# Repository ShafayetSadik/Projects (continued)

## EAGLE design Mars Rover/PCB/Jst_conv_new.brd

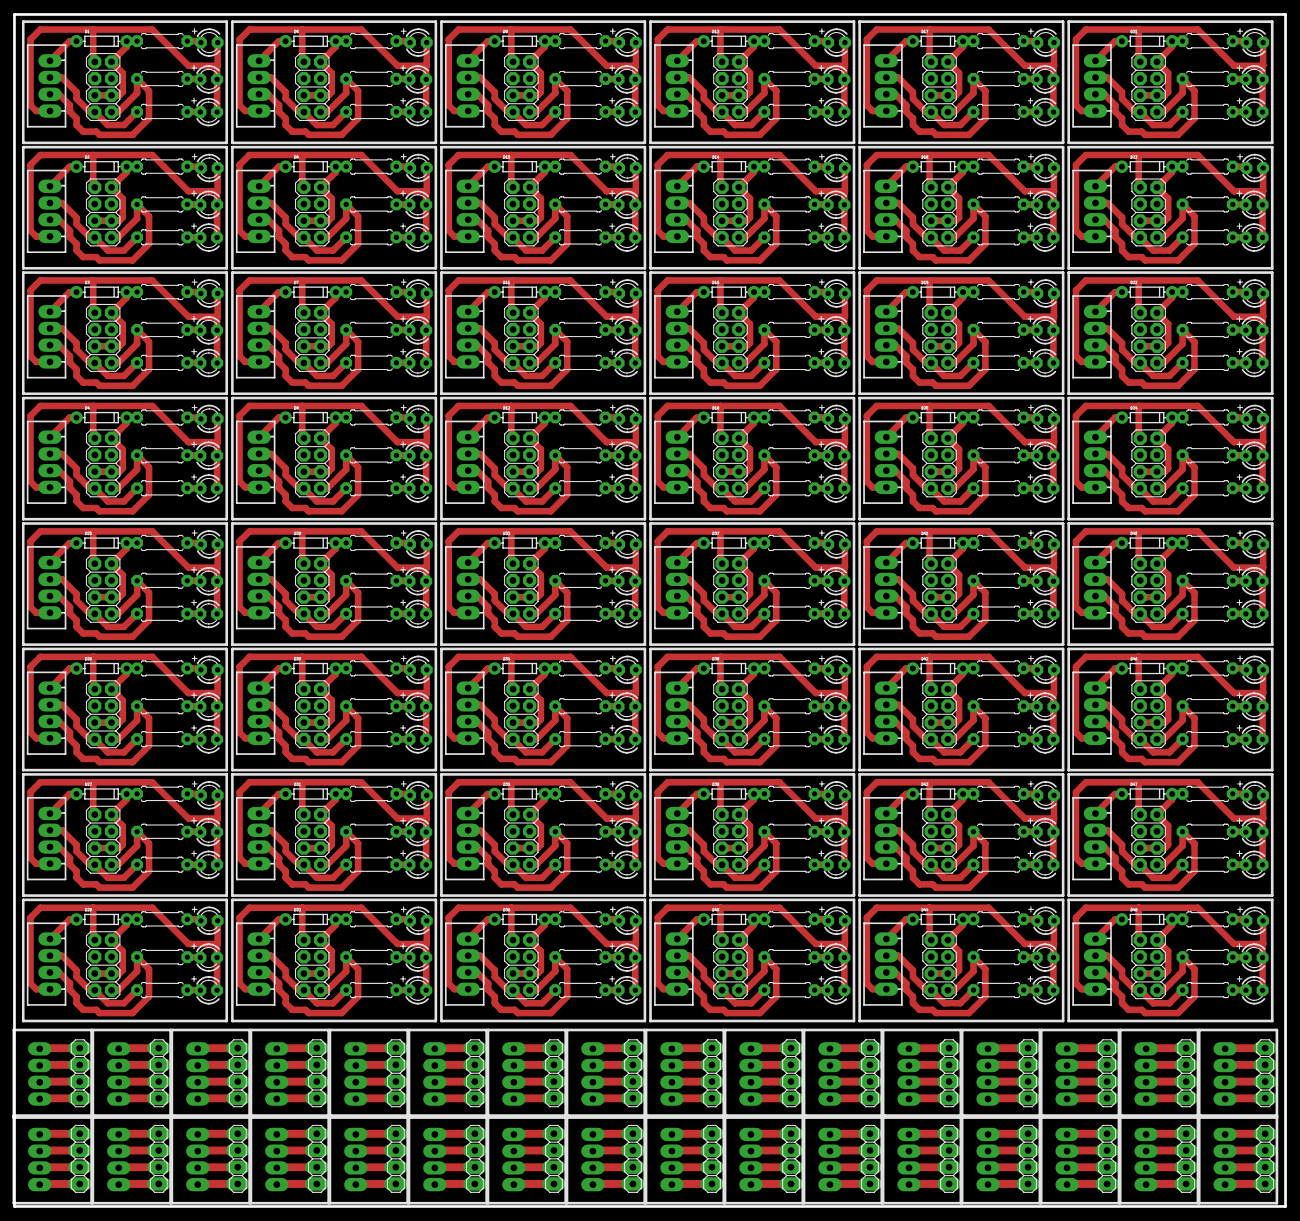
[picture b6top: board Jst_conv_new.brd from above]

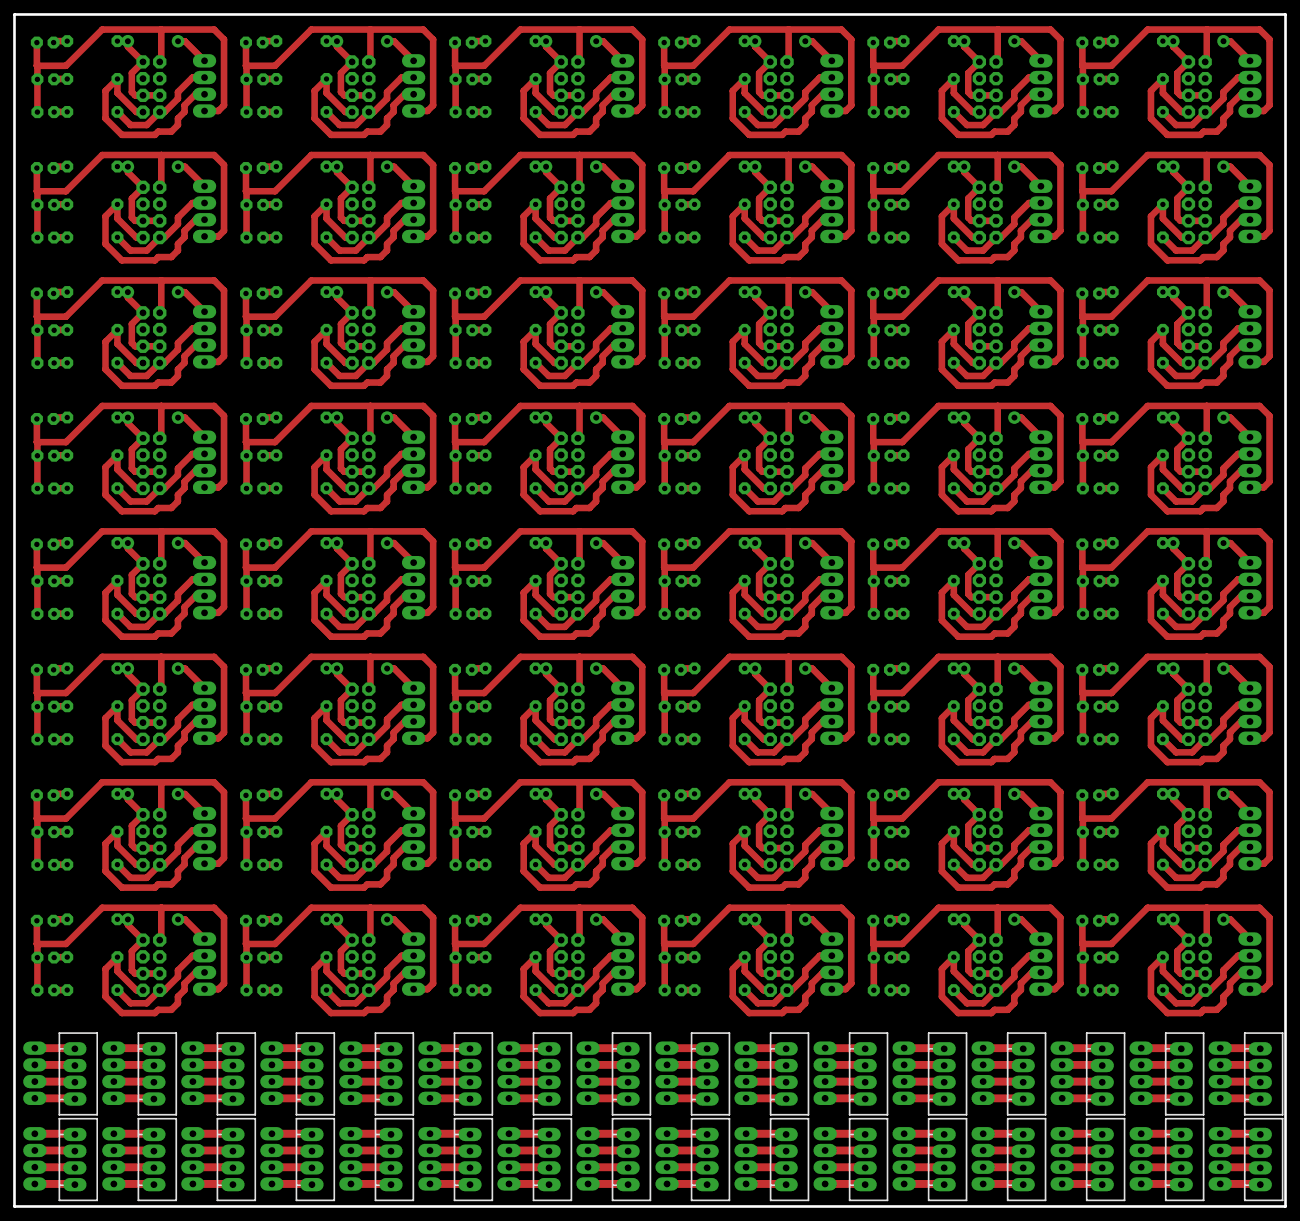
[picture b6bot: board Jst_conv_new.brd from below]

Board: 2 copper layers, 193.0 x 181.0 mm, 496 parts (32 on the bottom side), 512 nets.

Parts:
D1, D2, D3, D4, D5, D6, D7, D8, D9, D10, D11, D12, D13, D14, D15, D16, D17, D18, D19, D20, D21, D22, D23, D24, D25, D26, D27, D28, D29, D30, D31, D32, D33, D34, D35, D36, D37, D38, D39, D40, D41, D42, D43, D44, D45, D46, D47, D48: DO-1N4148
JP1, JP2, JP3, JP4, JP5, JP6, JP7, JP8, JP9, JP10, JP11, JP12, JP13, JP14, JP15, JP16, JP17, JP18, JP19, JP20, JP21, JP22, JP23, JP24, JP25, JP26, JP27, JP28, JP29, JP30, JP31, JP32, JP33, JP34, JP35, JP36, JP37, JP38, JP39, JP40, JP41, JP42, JP43, JP44, JP45, JP46, JP47, JP48: 2X04
JP49, JP50, JP51, JP52, JP53, JP54, JP55, JP56, JP57, JP58, JP59, JP60, JP61, JP62, JP63, JP64, JP65, JP66, JP67, JP68, JP69, JP70, JP71, JP72, JP73, JP74, JP75, JP76, JP77, JP78, JP79, JP80: 1X04
LED1, LED2, LED3, LED4, LED5, LED6, LED7, LED8, LED9, LED10, LED11, LED12, LED13, LED14, LED15, LED16, LED17, LED18, LED19, LED20, LED21, LED22, LED23, LED24, LED25, LED26, LED27, LED28, LED29, LED30, LED31, LED32, LED33, LED34, LED35, LED36, LED37, LED38, LED39, LED40, LED41, LED42, LED43, LED44, LED45, LED46, LED47, LED48, LED49, LED50, LED51, LED52, LED53, LED54, LED55, LED56, LED57, LED58, LED59, LED60, LED61, LED62, LED63, LED64, LED65, LED66, LED67, LED68, LED69, LED70, LED71, LED72, LED73, LED74, LED75, LED76, LED77, LED78, LED79, LED80, LED81, LED82, LED83, LED84, LED85, LED86, LED87, LED88, LED89, LED90, LED91, LED92, LED93, LED94, LED95, LED96, LED97, LED98, LED99, LED100, LED101, LED102, LED103, LED104, LED105, LED106, LED107, LED108, LED109, LED110, LED111, LED112, LED113, LED114, LED115, LED116, LED117, LED118, LED119, LED120, LED121, LED122, LED123, LED124, LED125, LED126, LED127, LED128, LED129, LED130, LED131, LED132, LED133, LED134, LED135, LED136, LED137, LED138, LED139, LED140, LED141, LED142, LED143, LED144: LED3MM
R1, R2, R3, R4, R5, R6, R7, R8, R9, R10, R11, R12, R13, R14, R15, R16, R17, R18, R19, R20, R21, R22, R23, R24, R25, R26, R27, R28, R29, R30, R31, R32, R33, R34, R35, R36, R37, R38, R39, R40, R41, R42, R43, R44, R45, R46, R47, R48, R49, R50, R51, R52, R53, R54, R55, R56, R57, R58, R59, R60, R61, R62, R63, R64, R65, R66, R67, R68, R69, R70, R71, R72, R73, R74, R75, R76, R77, R78, R79, R80, R81, R82, R83, R84, R85, R86, R87, R88, R89, R90, R91, R92, R93, R94, R95, R96, R97, R98, R99, R100, R101, R102, R103, R104, R105, R106, R107, R108, R109, R110, R111, R112, R113, R114, R115, R116, R117, R118, R119, R120, R121, R122, R123, R124, R125, R126, R127, R128, R129, R130, R131, R132, R133, R134, R135, R136, R137, R138, R139, R140, R141, R142, R143, R144: 0207/7
X1, X2, X3, X4, X5, X6, X7, X8, X9, X10, X11, X12, X13, X14, X15, X16, X17, X18, X19, X20, X21, X22, X23, X24, X25, X26, X27, X28, X29, X30, X31, X32, X33, X34, X35, X36, X37, X38, X39, X40, X41, X42, X43, X44, X45, X46, X47, X48, X49, X50, X51, X52, X53, X54, X55, X56, X57, X58, X59, X60, X61, X62, X63, X64, X65, X66, X67, X68, X69, X70, X71, X72, X73, X74, X75, X76, X77, X78, X79, X80: JST-XH-04-PIN-LONG-PAD; JST-XH-04-PACKAGE-LONG-PAD

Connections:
A: JP1.7, R6.2, X1.3
A1: JP2.7, R3.2, X2.3
A2: JP3.7, R9.2, X3.3
A3: JP4.7, R12.2, X4.3
A4: JP5.7, R15.2, X5.3
A5: JP6.7, R18.2, X6.3
A6: JP7.7, R21.2, X7.3
A7: JP8.7, R24.2, X8.3
A8: JP9.7, R27.2, X9.3
A9: JP10.7, R30.2, X10.3
A10: JP11.7, R33.2, X11.3
A11: JP12.7, R36.2, X12.3
A12: JP13.7, R39.2, X13.3
A13: JP14.7, R42.2, X14.3
A14: JP15.7, R45.2, X15.3
A15: JP16.7, R48.2, X16.3
A16: JP17.7, R51.2, X17.3
A17: JP18.7, R54.2, X18.3
A18: JP19.7, R57.2, X19.3
A19: JP20.7, R60.2, X20.3
A20: JP21.7, R63.2, X21.3
A21: JP22.7, R66.2, X22.3
A22: JP23.7, R69.2, X23.3
A23: JP24.7, R72.2, X24.3
A24: JP25.7, R75.2, X25.3
A25: JP26.7, R78.2, X26.3
A26: JP27.7, R81.2, X27.3
A27: JP28.7, R84.2, X28.3
A28: JP29.7, R87.2, X29.3
A29: JP30.7, R90.2, X30.3
A30: JP31.7, R93.2, X31.3
A31: JP32.7, R96.2, X32.3
A32: JP33.7, R99.2, X33.3
A33: JP34.7, R102.2, X34.3
A34: JP35.7, R105.2, X35.3
A35: JP36.7, R108.2, X36.3
A36: JP37.7, R111.2, X37.3
A37: JP38.7, R114.2, X38.3
A38: JP39.7, R117.2, X39.3
A39: JP40.7, R120.2, X40.3
A40: JP41.7, R123.2, X41.3
A41: JP42.7, R126.2, X42.3
A42: JP43.7, R129.2, X43.3
A43: JP44.7, R132.2, X44.3
A44: JP45.7, R135.2, X45.3
A45: JP46.7, R138.2, X46.3
A46: JP47.7, R141.2, X47.3
A47: JP48.7, R144.2, X48.3
B: JP1.8, R4.2, X1.2
B1: JP2.8, R1.2, X2.2
B2: JP3.8, R7.2, X3.2
B3: JP4.8, R10.2, X4.2
B4: JP5.8, R13.2, X5.2
B5: JP6.8, R16.2, X6.2
B6: JP7.8, R19.2, X7.2
B7: JP8.8, R22.2, X8.2
B8: JP9.8, R25.2, X9.2
B9: JP10.8, R28.2, X10.2
B10: JP11.8, R31.2, X11.2
B11: JP12.8, R34.2, X12.2
B12: JP13.8, R37.2, X13.2
B13: JP14.8, R40.2, X14.2
B14: JP15.8, R43.2, X15.2
B15: JP16.8, R46.2, X16.2
B16: JP17.8, R49.2, X17.2
B17: JP18.8, R52.2, X18.2
B18: JP19.8, R55.2, X19.2
B19: JP20.8, R58.2, X20.2
B20: JP21.8, R61.2, X21.2
B21: JP22.8, R64.2, X22.2
B22: JP23.8, R67.2, X23.2
B23: JP24.8, R70.2, X24.2
B24: JP25.8, R73.2, X25.2
B25: JP26.8, R76.2, X26.2
B26: JP27.8, R79.2, X27.2
B27: JP28.8, R82.2, X28.2
B28: JP29.8, R85.2, X29.2
B29: JP30.8, R88.2, X30.2
B30: JP31.8, R91.2, X31.2
B31: JP32.8, R94.2, X32.2
B32: JP33.8, R97.2, X33.2
B33: JP34.8, R100.2, X34.2
B34: JP35.8, R103.2, X35.2
B35: JP36.8, R106.2, X36.2
B36: JP37.8, R109.2, X37.2
B37: JP38.8, R112.2, X38.2
B38: JP39.8, R115.2, X39.2
B39: JP40.8, R118.2, X40.2
B40: JP41.8, R121.2, X41.2
B41: JP42.8, R124.2, X42.2
B42: JP43.8, R127.2, X43.2
B43: JP44.8, R130.2, X44.2
B44: JP45.8, R133.2, X45.2
B45: JP46.8, R136.2, X46.2
B46: JP47.8, R139.2, X47.2
B47: JP48.8, R142.2, X48.2
GND: JP1.1, LED1.K, LED2.K, LED3.K, X1.1
GND1: JP2.1, LED4.K, LED5.K, LED6.K, X2.1
GND2: JP3.1, LED7.K, LED8.K, LED9.K, X3.1
GND3: JP4.1, LED10.K, LED11.K, LED12.K, X4.1
GND4: JP5.1, LED13.K, LED14.K, LED15.K, X5.1
GND5: JP6.1, LED16.K, LED17.K, LED18.K, X6.1
GND6: JP7.1, LED19.K, LED20.K, LED21.K, X7.1
GND7: JP8.1, LED22.K, LED23.K, LED24.K, X8.1
GND8: JP9.1, LED25.K, LED26.K, LED27.K, X9.1
GND9: JP10.1, LED28.K, LED29.K, LED30.K, X10.1
GND10: JP11.1, LED31.K, LED32.K, LED33.K, X11.1
GND11: JP12.1, LED34.K, LED35.K, LED36.K, X12.1
GND12: JP13.1, LED37.K, LED38.K, LED39.K, X13.1
GND13: JP14.1, LED40.K, LED41.K, LED42.K, X14.1
GND14: JP15.1, LED43.K, LED44.K, LED45.K, X15.1
GND15: JP16.1, LED46.K, LED47.K, LED48.K, X16.1
GND16: JP17.1, LED49.K, LED50.K, LED51.K, X17.1
GND17: JP18.1, LED52.K, LED53.K, LED54.K, X18.1
GND18: JP19.1, LED55.K, LED56.K, LED57.K, X19.1
GND19: JP20.1, LED58.K, LED59.K, LED60.K, X20.1
GND20: JP21.1, LED61.K, LED62.K, LED63.K, X21.1
GND21: JP22.1, LED64.K, LED65.K, LED66.K, X22.1
GND22: JP23.1, LED67.K, LED68.K, LED69.K, X23.1
GND23: JP24.1, LED70.K, LED71.K, LED72.K, X24.1
GND24: JP25.1, LED73.K, LED74.K, LED75.K, X25.1
GND25: JP26.1, LED76.K, LED77.K, LED78.K, X26.1
GND26: JP27.1, LED79.K, LED80.K, LED81.K, X27.1
GND27: JP28.1, LED82.K, LED83.K, LED84.K, X28.1
GND28: JP29.1, LED85.K, LED86.K, LED87.K, X29.1
GND29: JP30.1, LED88.K, LED89.K, LED90.K, X30.1
GND30: JP31.1, LED91.K, LED92.K, LED93.K, X31.1
GND31: JP32.1, LED94.K, LED95.K, LED96.K, X32.1
GND32: JP33.1, LED97.K, LED98.K, LED99.K, X33.1
GND33: JP34.1, LED100.K, LED101.K, LED102.K, X34.1
GND34: JP35.1, LED103.K, LED104.K, LED105.K, X35.1
GND35: JP36.1, LED106.K, LED107.K, LED108.K, X36.1
GND36: JP37.1, LED109.K, LED110.K, LED111.K, X37.1
GND37: JP38.1, LED112.K, LED113.K, LED114.K, X38.1
GND38: JP39.1, LED115.K, LED116.K, LED117.K, X39.1
GND39: JP40.1, LED118.K, LED119.K, LED120.K, X40.1
GND40: JP41.1, LED121.K, LED122.K, LED123.K, X41.1
GND41: JP42.1, LED124.K, LED125.K, LED126.K, X42.1
GND42: JP43.1, LED127.K, LED128.K, LED129.K, X43.1
GND43: JP44.1, LED130.K, LED131.K, LED132.K, X44.1
GND44: JP45.1, LED133.K, LED134.K, LED135.K, X45.1
GND45: JP46.1, LED136.K, LED137.K, LED138.K, X46.1
GND46: JP47.1, LED139.K, LED140.K, LED141.K, X47.1
GND47: JP48.1, LED142.K, LED143.K, LED144.K, X48.1
unnamed: D1.A, X1.4
unnamed: LED6.A, R2.1
unnamed: LED5.A, R3.1
unnamed: LED4.A, R1.1
unnamed: D2.A, X2.4
unnamed: LED3.A, R5.1
unnamed: LED2.A, R6.1
unnamed: LED1.A, R4.1
unnamed: LED9.A, R8.1
unnamed: LED8.A, R9.1
unnamed: LED7.A, R7.1
unnamed: D3.A, X3.4
unnamed: LED12.A, R11.1
unnamed: LED11.A, R12.1
unnamed: LED10.A, R10.1
unnamed: D4.A, X4.4
unnamed: LED15.A, R14.1
unnamed: LED14.A, R15.1
unnamed: LED13.A, R13.1
unnamed: D5.A, X5.4
unnamed: LED18.A, R17.1
unnamed: LED17.A, R18.1
unnamed: LED16.A, R16.1
unnamed: D6.A, X6.4
unnamed: LED21.A, R20.1
unnamed: LED20.A, R21.1
unnamed: LED19.A, R19.1
unnamed: D7.A, X7.4
unnamed: LED24.A, R23.1
unnamed: LED23.A, R24.1
unnamed: LED22.A, R22.1
unnamed: D8.A, X8.4
unnamed: LED27.A, R26.1
unnamed: LED26.A, R27.1
unnamed: LED25.A, R25.1
unnamed: D9.A, X9.4
unnamed: LED30.A, R29.1
unnamed: LED29.A, R30.1
unnamed: LED28.A, R28.1
unnamed: D10.A, X10.4
unnamed: LED33.A, R32.1
unnamed: LED32.A, R33.1
unnamed: LED31.A, R31.1
unnamed: D11.A, X11.4
unnamed: LED36.A, R35.1
unnamed: LED35.A, R36.1
unnamed: LED34.A, R34.1
unnamed: D12.A, X12.4
unnamed: LED39.A, R38.1
unnamed: LED38.A, R39.1
unnamed: LED37.A, R37.1
unnamed: D13.A, X13.4
unnamed: LED42.A, R41.1
unnamed: LED41.A, R42.1
unnamed: LED40.A, R40.1
unnamed: D14.A, X14.4
unnamed: LED45.A, R44.1
unnamed: LED44.A, R45.1
unnamed: LED43.A, R43.1
unnamed: D15.A, X15.4
unnamed: LED48.A, R47.1
unnamed: LED47.A, R48.1
unnamed: LED46.A, R46.1
unnamed: D16.A, X16.4
unnamed: LED51.A, R50.1
unnamed: LED50.A, R51.1
unnamed: LED49.A, R49.1
unnamed: D17.A, X17.4
unnamed: LED54.A, R53.1
unnamed: LED53.A, R54.1
unnamed: LED52.A, R52.1
unnamed: D18.A, X18.4
unnamed: LED57.A, R56.1
unnamed: LED56.A, R57.1
unnamed: LED55.A, R55.1
unnamed: D19.A, X19.4
unnamed: LED60.A, R59.1
unnamed: LED59.A, R60.1
unnamed: LED58.A, R58.1
unnamed: D20.A, X20.4
unnamed: LED63.A, R62.1
unnamed: LED62.A, R63.1
unnamed: LED61.A, R61.1
unnamed: D21.A, X21.4
unnamed: LED66.A, R65.1
unnamed: LED65.A, R66.1
unnamed: LED64.A, R64.1
unnamed: D22.A, X22.4
unnamed: LED69.A, R68.1
unnamed: LED68.A, R69.1
unnamed: LED67.A, R67.1
unnamed: D23.A, X23.4
unnamed: LED72.A, R71.1
unnamed: LED71.A, R72.1
unnamed: LED70.A, R70.1
unnamed: D24.A, X24.4
unnamed: LED75.A, R74.1
unnamed: LED74.A, R75.1
unnamed: LED73.A, R73.1
unnamed: D25.A, X25.4
unnamed: LED78.A, R77.1
unnamed: LED77.A, R78.1
unnamed: LED76.A, R76.1
unnamed: D26.A, X26.4
unnamed: LED81.A, R80.1
unnamed: LED80.A, R81.1
unnamed: LED79.A, R79.1
unnamed: D27.A, X27.4
unnamed: LED84.A, R83.1
unnamed: LED83.A, R84.1
unnamed: LED82.A, R82.1
unnamed: D28.A, X28.4
unnamed: LED87.A, R86.1
unnamed: LED86.A, R87.1
unnamed: LED85.A, R85.1
unnamed: D29.A, X29.4
unnamed: LED90.A, R89.1
unnamed: LED89.A, R90.1
unnamed: LED88.A, R88.1
unnamed: D30.A, X30.4
unnamed: LED93.A, R92.1
unnamed: LED92.A, R93.1
unnamed: LED91.A, R91.1
unnamed: D31.A, X31.4
unnamed: LED96.A, R95.1
unnamed: LED95.A, R96.1
unnamed: LED94.A, R94.1
unnamed: D32.A, X32.4
unnamed: LED99.A, R98.1
unnamed: LED98.A, R99.1
unnamed: LED97.A, R97.1
unnamed: D33.A, X33.4
unnamed: LED102.A, R101.1
unnamed: LED101.A, R102.1
unnamed: LED100.A, R100.1
unnamed: D34.A, X34.4
unnamed: LED105.A, R104.1
unnamed: LED104.A, R105.1
unnamed: LED103.A, R103.1
unnamed: D35.A, X35.4
unnamed: LED108.A, R107.1
unnamed: LED107.A, R108.1
unnamed: LED106.A, R106.1
unnamed: D36.A, X36.4
unnamed: LED111.A, R110.1
unnamed: LED110.A, R111.1
unnamed: LED109.A, R109.1
unnamed: D37.A, X37.4
unnamed: LED114.A, R113.1
unnamed: LED113.A, R114.1
unnamed: LED112.A, R112.1
unnamed: D38.A, X38.4
unnamed: LED117.A, R116.1
unnamed: LED116.A, R117.1
unnamed: LED115.A, R115.1
unnamed: D39.A, X39.4
unnamed: LED120.A, R119.1
unnamed: LED119.A, R120.1
unnamed: LED118.A, R118.1
unnamed: D40.A, X40.4
unnamed: LED123.A, R122.1
unnamed: LED122.A, R123.1
unnamed: LED121.A, R121.1
unnamed: D41.A, X41.4
unnamed: LED126.A, R125.1
unnamed: LED125.A, R126.1
unnamed: LED124.A, R124.1
unnamed: D42.A, X42.4
unnamed: LED129.A, R128.1
unnamed: LED128.A, R129.1
unnamed: LED127.A, R127.1
unnamed: D43.A, X43.4
unnamed: LED132.A, R131.1
unnamed: LED131.A, R132.1
unnamed: LED130.A, R130.1
unnamed: D44.A, X44.4
unnamed: LED135.A, R134.1
unnamed: LED134.A, R135.1
unnamed: LED133.A, R133.1
unnamed: D45.A, X45.4
unnamed: LED138.A, R137.1
unnamed: LED137.A, R138.1
unnamed: LED136.A, R136.1
unnamed: D46.A, X46.4
unnamed: LED141.A, R140.1
unnamed: LED140.A, R141.1
unnamed: LED139.A, R139.1
unnamed: D47.A, X47.4
unnamed: LED144.A, R143.1
unnamed: LED143.A, R144.1
unnamed: LED142.A, R142.1
unnamed: D48.A, X48.4
unnamed: JP49.1, X49.1
unnamed: JP49.4, X49.4
unnamed: JP49.2, X49.2
unnamed: JP49.3, X49.3
unnamed: JP50.1, X50.1
unnamed: JP50.4, X50.4
unnamed: JP50.2, X50.2
unnamed: JP50.3, X50.3
unnamed: JP51.1, X51.1
unnamed: JP51.4, X51.4
unnamed: JP51.2, X51.2
unnamed: JP51.3, X51.3
unnamed: JP52.1, X52.1
unnamed: JP52.4, X52.4
unnamed: JP52.2, X52.2
unnamed: JP52.3, X52.3
unnamed: JP53.1, X53.1
unnamed: JP53.4, X53.4
unnamed: JP53.2, X53.2
unnamed: JP53.3, X53.3
unnamed: JP54.1, X54.1
unnamed: JP54.4, X54.4
unnamed: JP54.2, X54.2
unnamed: JP54.3, X54.3
unnamed: JP55.1, X55.1
unnamed: JP55.4, X55.4
unnamed: JP55.2, X55.2
unnamed: JP55.3, X55.3
unnamed: JP56.1, X56.1
unnamed: JP56.4, X56.4
unnamed: JP56.2, X56.2
unnamed: JP56.3, X56.3
unnamed: JP57.1, X57.1
unnamed: JP57.4, X57.4
unnamed: JP57.2, X57.2
unnamed: JP57.3, X57.3
unnamed: JP58.1, X58.1
unnamed: JP58.4, X58.4
unnamed: JP58.2, X58.2
unnamed: JP58.3, X58.3
unnamed: JP59.1, X59.1
unnamed: JP59.4, X59.4
unnamed: JP59.2, X59.2
unnamed: JP59.3, X59.3
unnamed: JP60.1, X60.1
unnamed: JP60.4, X60.4
unnamed: JP60.2, X60.2
unnamed: JP60.3, X60.3
unnamed: JP61.1, X61.1
unnamed: JP61.4, X61.4
unnamed: JP61.2, X61.2
unnamed: JP61.3, X61.3
unnamed: JP62.1, X62.1
unnamed: JP62.4, X62.4
unnamed: JP62.2, X62.2
unnamed: JP62.3, X62.3
unnamed: JP63.1, X63.1
unnamed: JP63.4, X63.4
unnamed: JP63.2, X63.2
unnamed: JP63.3, X63.3
unnamed: JP64.1, X64.1
unnamed: JP64.4, X64.4
unnamed: JP64.2, X64.2
unnamed: JP64.3, X64.3
unnamed: JP65.1, X65.1
unnamed: JP65.4, X65.4
unnamed: JP65.2, X65.2
unnamed: JP65.3, X65.3
unnamed: JP66.1, X66.1
unnamed: JP66.4, X66.4
unnamed: JP66.2, X66.2
unnamed: JP66.3, X66.3
unnamed: JP67.1, X67.1
unnamed: JP67.4, X67.4
unnamed: JP67.2, X67.2
unnamed: JP67.3, X67.3
unnamed: JP68.1, X68.1
unnamed: JP68.4, X68.4
unnamed: JP68.2, X68.2
unnamed: JP68.3, X68.3
unnamed: JP69.1, X69.1
unnamed: JP69.4, X69.4
unnamed: JP69.2, X69.2
unnamed: JP69.3, X69.3
unnamed: JP70.1, X70.1
unnamed: JP70.4, X70.4
unnamed: JP70.2, X70.2
unnamed: JP70.3, X70.3
unnamed: JP71.1, X71.1
unnamed: JP71.4, X71.4
unnamed: JP71.2, X71.2
unnamed: JP71.3, X71.3
unnamed: JP72.1, X72.1
unnamed: JP72.4, X72.4
unnamed: JP72.2, X72.2
unnamed: JP72.3, X72.3
unnamed: JP73.1, X73.1
unnamed: JP73.4, X73.4
unnamed: JP73.2, X73.2
unnamed: JP73.3, X73.3
unnamed: JP74.1, X74.1
unnamed: JP74.4, X74.4
unnamed: JP74.2, X74.2
unnamed: JP74.3, X74.3
unnamed: JP75.1, X75.1
unnamed: JP75.4, X75.4
unnamed: JP75.2, X75.2
unnamed: JP75.3, X75.3
unnamed: JP76.1, X76.1
unnamed: JP76.4, X76.4
unnamed: JP76.2, X76.2
unnamed: JP76.3, X76.3
unnamed: JP77.1, X77.1
unnamed: JP77.4, X77.4
unnamed: JP77.2, X77.2
unnamed: JP77.3, X77.3
unnamed: JP78.1, X78.1
unnamed: JP78.4, X78.4
unnamed: JP78.2, X78.2
unnamed: JP78.3, X78.3
unnamed: JP79.1, X79.1
unnamed: JP79.4, X79.4
unnamed: JP79.2, X79.2
unnamed: JP79.3, X79.3
unnamed: JP80.1, X80.1
unnamed: JP80.4, X80.4
unnamed: JP80.2, X80.2
unnamed: JP80.3, X80.3
VCC: D1.C, JP1.2, JP1.5, JP1.6, R5.2
VCC1: D2.C, JP2.2, JP2.5, JP2.6, R2.2
VCC2: D3.C, JP3.2, JP3.5, JP3.6, R8.2
VCC3: D4.C, JP4.2, JP4.5, JP4.6, R11.2
VCC4: D5.C, JP5.2, JP5.5, JP5.6, R14.2
VCC5: D6.C, JP6.2, JP6.5, JP6.6, R17.2
VCC6: D7.C, JP7.2, JP7.5, JP7.6, R20.2
VCC7: D8.C, JP8.2, JP8.5, JP8.6, R23.2
VCC8: D9.C, JP9.2, JP9.5, JP9.6, R26.2
VCC9: D10.C, JP10.2, JP10.5, JP10.6, R29.2
VCC10: D11.C, JP11.2, JP11.5, JP11.6, R32.2
VCC11: D12.C, JP12.2, JP12.5, JP12.6, R35.2
VCC12: D13.C, JP13.2, JP13.5, JP13.6, R38.2
VCC13: D14.C, JP14.2, JP14.5, JP14.6, R41.2
VCC14: D15.C, JP15.2, JP15.5, JP15.6, R44.2
VCC15: D16.C, JP16.2, JP16.5, JP16.6, R47.2
VCC16: D17.C, JP17.2, JP17.5, JP17.6, R50.2
VCC17: D18.C, JP18.2, JP18.5, JP18.6, R53.2
VCC18: D19.C, JP19.2, JP19.5, JP19.6, R56.2
VCC19: D20.C, JP20.2, JP20.5, JP20.6, R59.2
VCC20: D21.C, JP21.2, JP21.5, JP21.6, R62.2
VCC21: D22.C, JP22.2, JP22.5, JP22.6, R65.2
VCC22: D23.C, JP23.2, JP23.5, JP23.6, R68.2
VCC23: D24.C, JP24.2, JP24.5, JP24.6, R71.2
VCC24: D25.C, JP25.2, JP25.5, JP25.6, R74.2
VCC25: D26.C, JP26.2, JP26.5, JP26.6, R77.2
VCC26: D27.C, JP27.2, JP27.5, JP27.6, R80.2
VCC27: D28.C, JP28.2, JP28.5, JP28.6, R83.2
VCC28: D29.C, JP29.2, JP29.5, JP29.6, R86.2
VCC29: D30.C, JP30.2, JP30.5, JP30.6, R89.2
VCC30: D31.C, JP31.2, JP31.5, JP31.6, R92.2
VCC31: D32.C, JP32.2, JP32.5, JP32.6, R95.2
VCC32: D33.C, JP33.2, JP33.5, JP33.6, R98.2
VCC33: D34.C, JP34.2, JP34.5, JP34.6, R101.2
VCC34: D35.C, JP35.2, JP35.5, JP35.6, R104.2
VCC35: D36.C, JP36.2, JP36.5, JP36.6, R107.2
VCC36: D37.C, JP37.2, JP37.5, JP37.6, R110.2
VCC37: D38.C, JP38.2, JP38.5, JP38.6, R113.2
VCC38: D39.C, JP39.2, JP39.5, JP39.6, R116.2
VCC39: D40.C, JP40.2, JP40.5, JP40.6, R119.2
VCC40: D41.C, JP41.2, JP41.5, JP41.6, R122.2
VCC41: D42.C, JP42.2, JP42.5, JP42.6, R125.2
VCC42: D43.C, JP43.2, JP43.5, JP43.6, R128.2
VCC43: D44.C, JP44.2, JP44.5, JP44.6, R131.2
VCC44: D45.C, JP45.2, JP45.5, JP45.6, R134.2
VCC45: D46.C, JP46.2, JP46.5, JP46.6, R137.2
VCC46: D47.C, JP47.2, JP47.5, JP47.6, R140.2
VCC47: D48.C, JP48.2, JP48.5, JP48.6, R143.2

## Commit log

2026-04-21 academic projects
2026-04-21 more
2026-04-21 extra
2026-04-21 readme
2026-04-28 pics
2026-04-28 drone
2026-04-28 solar
2026-04-28 gait
2026-04-28 latest
2026-04-29 Rover
2026-04-29 slam
